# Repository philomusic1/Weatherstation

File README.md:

A unique weatherstation designed to program a motherboard.
This unique weatherstation has many abilities including the following:

-> A wemoss C3 mini.

-> A temprature sensor.

-> A humidity sensor.

These unique abilities allow it to enhance the user experience and make life easier as you can now check the weather without any internet. 

Will be updated with photos when the PCB arrives

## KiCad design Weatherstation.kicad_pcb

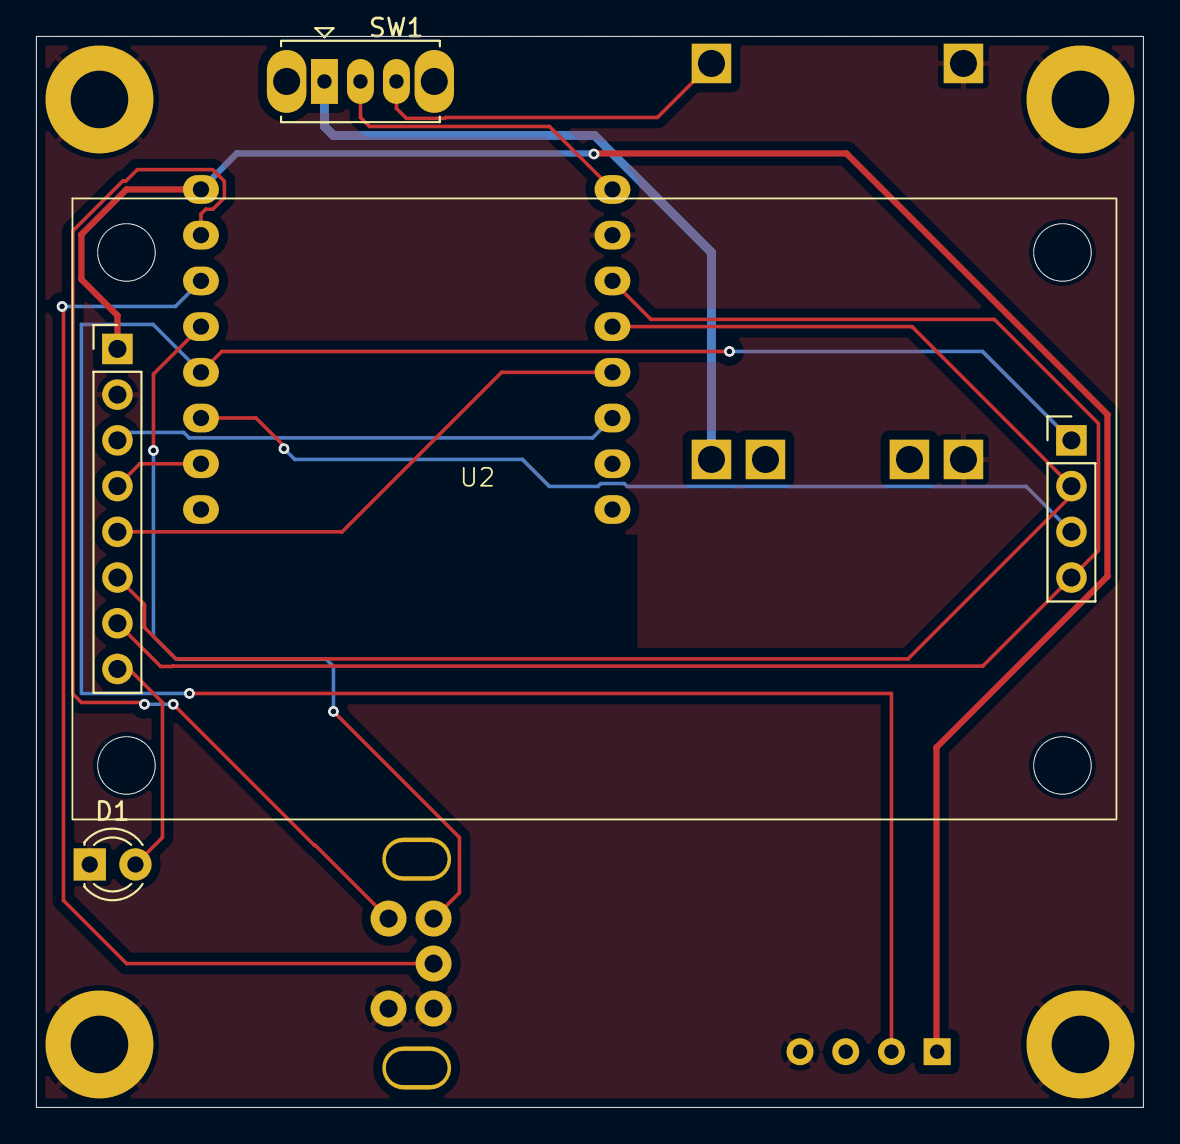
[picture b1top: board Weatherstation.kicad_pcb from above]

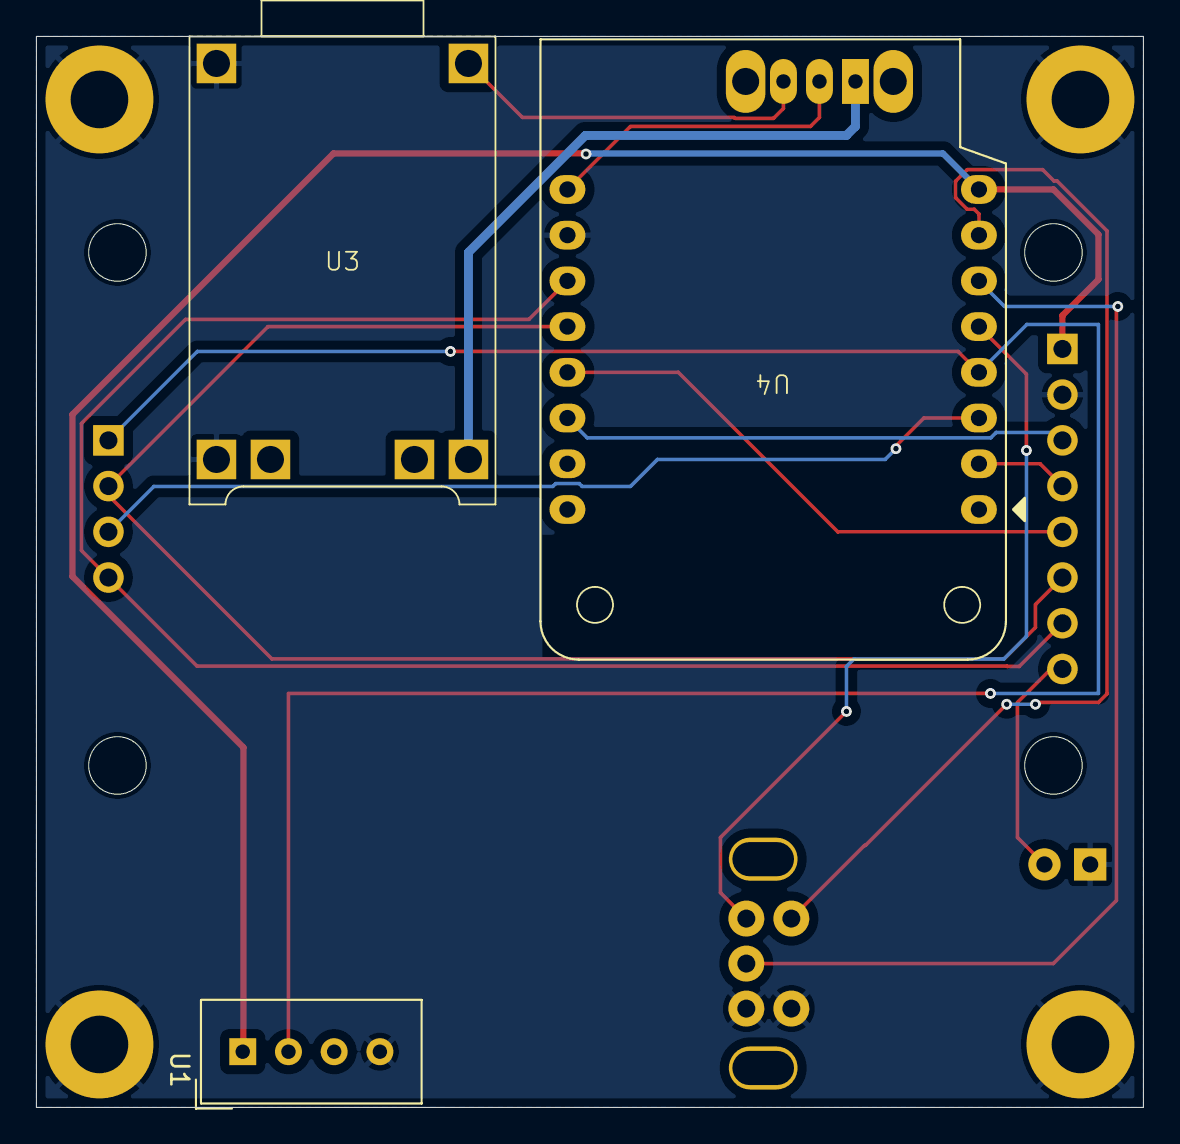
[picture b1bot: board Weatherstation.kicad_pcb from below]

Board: 2 copper layers, 61.5 x 59.5 mm, 11 parts (3 on the bottom side), 16 nets.

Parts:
D1: LED_3mm; LED_D3.0mm
H1, H2, H3, H4: MountingHole_M3_3.2mm_Pad; MountingHole_3.2mm_Pad
SW1: SW_SPDT; SW_Slide_SPDT_Straight_CK_OS102011MS2Q
U1: DHT11; Aosong_DHT11_5.5x12.0_P2.54mm
U2: TFT_ST7735_SD
U3: TP4056
U4: WEMOS_C3_Mini; WEMOS_C3_mini
U5: EC11B; RotaryEncoder_EC11B-Horizontal-Dual

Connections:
+3V3: U1.1 (VDD), U2.1 (3V3), U4.8 (3V3)
CS: U2.3 (LCD_CS), U2.9 (SD_CS), U4.14 (CS0/IO10)
DATA: U1.2 (DATA), U4.4 (IO1)
D/C: U2.5 (D/C), U4.13 (IO8)
EN: U2.4 (EN), U4.2 (IO3)
ENC_A: U4.5 (IO0), U5.B
ENC_B: U4.6 (IO4), U5.C
ENC_C: U4.7 (IO5), U5.S2
GND: D1.1, H1.1, H2.1, H3.1, H4.1, U1.4 (GND), U2.2 (GND), U3.3 (OUT-), U3.5 (IN-), U4.10 (GND), U5.A, U5.S1
MISO: U2.11 (SD_MISO), U4.3 (MISO/IO2)
MOSI: U2.6 (LCD_MOSI), U2.10 (SD_MOSI), U4.12 (MOSI/IO7)
unnamed: SW1.2 (B), U4.9 (5V)
unnamed: D1.2, U2.8 (LED)
SCK: U2.7 (LCD_SCK), U2.12 (SD_SCK), U4.11 (SCK/IO6)
TP_input: SW1.3 (C), U3.4 (IN+)
VCC: SW1.1 (A), U3.2 (OUT+)

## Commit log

2024-12-18 initial pcb setup
2024-12-22 add case and code
